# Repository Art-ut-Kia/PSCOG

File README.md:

# PSCOG (Power Supply Cutoff Generator)

This arduino-based project is a lab tool that permits to generate short power supply interruptions to test hold-up circuitry of airborne equipment.

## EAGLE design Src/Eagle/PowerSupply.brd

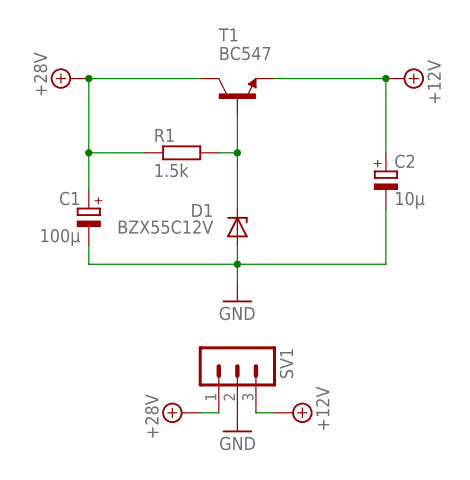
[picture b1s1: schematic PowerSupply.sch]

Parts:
C1: 100µ; E5-10,5
C2: 10µ; E5-8,5
D1: BZX55C12V; DO35Z10
R1: 1.5k; 0309/12
SV1: MA03-1
T1: BC547; TO92

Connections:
+12V: C2.+, SV1.3, T1.1 (E)
+28V: C1.+, R1.1, SV1.1, T1.3 (C)
GND: C1.-, C2.-, D1.A, SV1.2
unnamed: D1.C, R1.2, T1.2 (B)

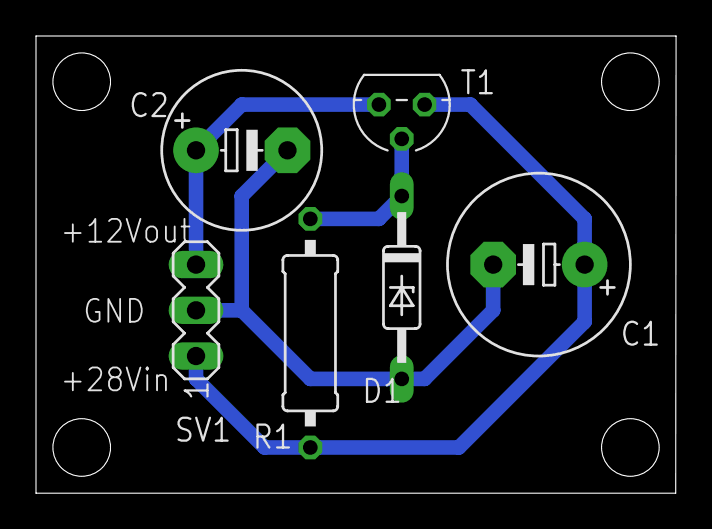
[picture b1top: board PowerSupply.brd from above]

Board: 2 copper layers, 35.6 x 25.4 mm, 6 parts (0 on the bottom side), 4 nets.

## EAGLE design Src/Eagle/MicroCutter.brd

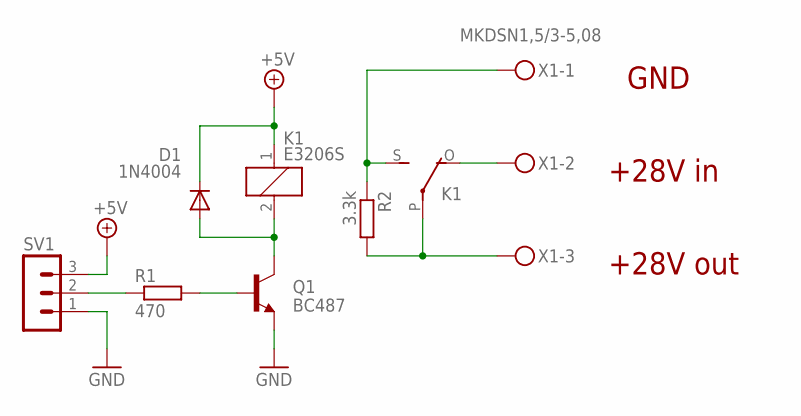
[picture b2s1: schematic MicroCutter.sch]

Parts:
D1: 1N4004; DO41-10
K1: E3206S
Q1: BC487; TO92-EBC
R1: 470; 0309/12
R2: 3.3k; 0309/12
SV1: MA03-1
X1: MKDSN1,5/3-5,08

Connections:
+5V: D1.C, K1.1, SV1.3
GND: Q1.E, SV1.1
unnamed: D1.A, K1.2, Q1.C
unnamed: K1.P, R2.2, X1.3
unnamed: K1.O, X1.2
unnamed: K1.S, R2.1, X1.1
unnamed: Q1.B, R1.2
unnamed: R1.1, SV1.2

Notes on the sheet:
+28V in
GND
+28V out

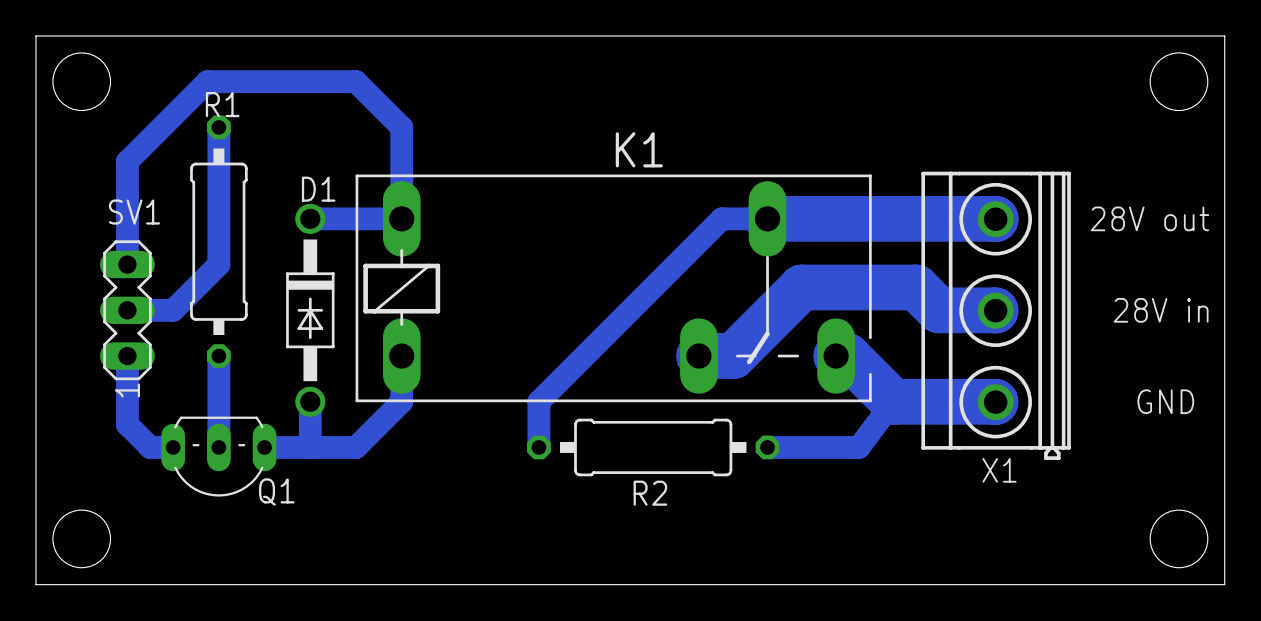
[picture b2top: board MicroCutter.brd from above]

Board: 2 copper layers, 66.0 x 30.5 mm, 7 parts (0 on the bottom side), 8 nets.

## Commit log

2016-11-06 Arduino Firmware
